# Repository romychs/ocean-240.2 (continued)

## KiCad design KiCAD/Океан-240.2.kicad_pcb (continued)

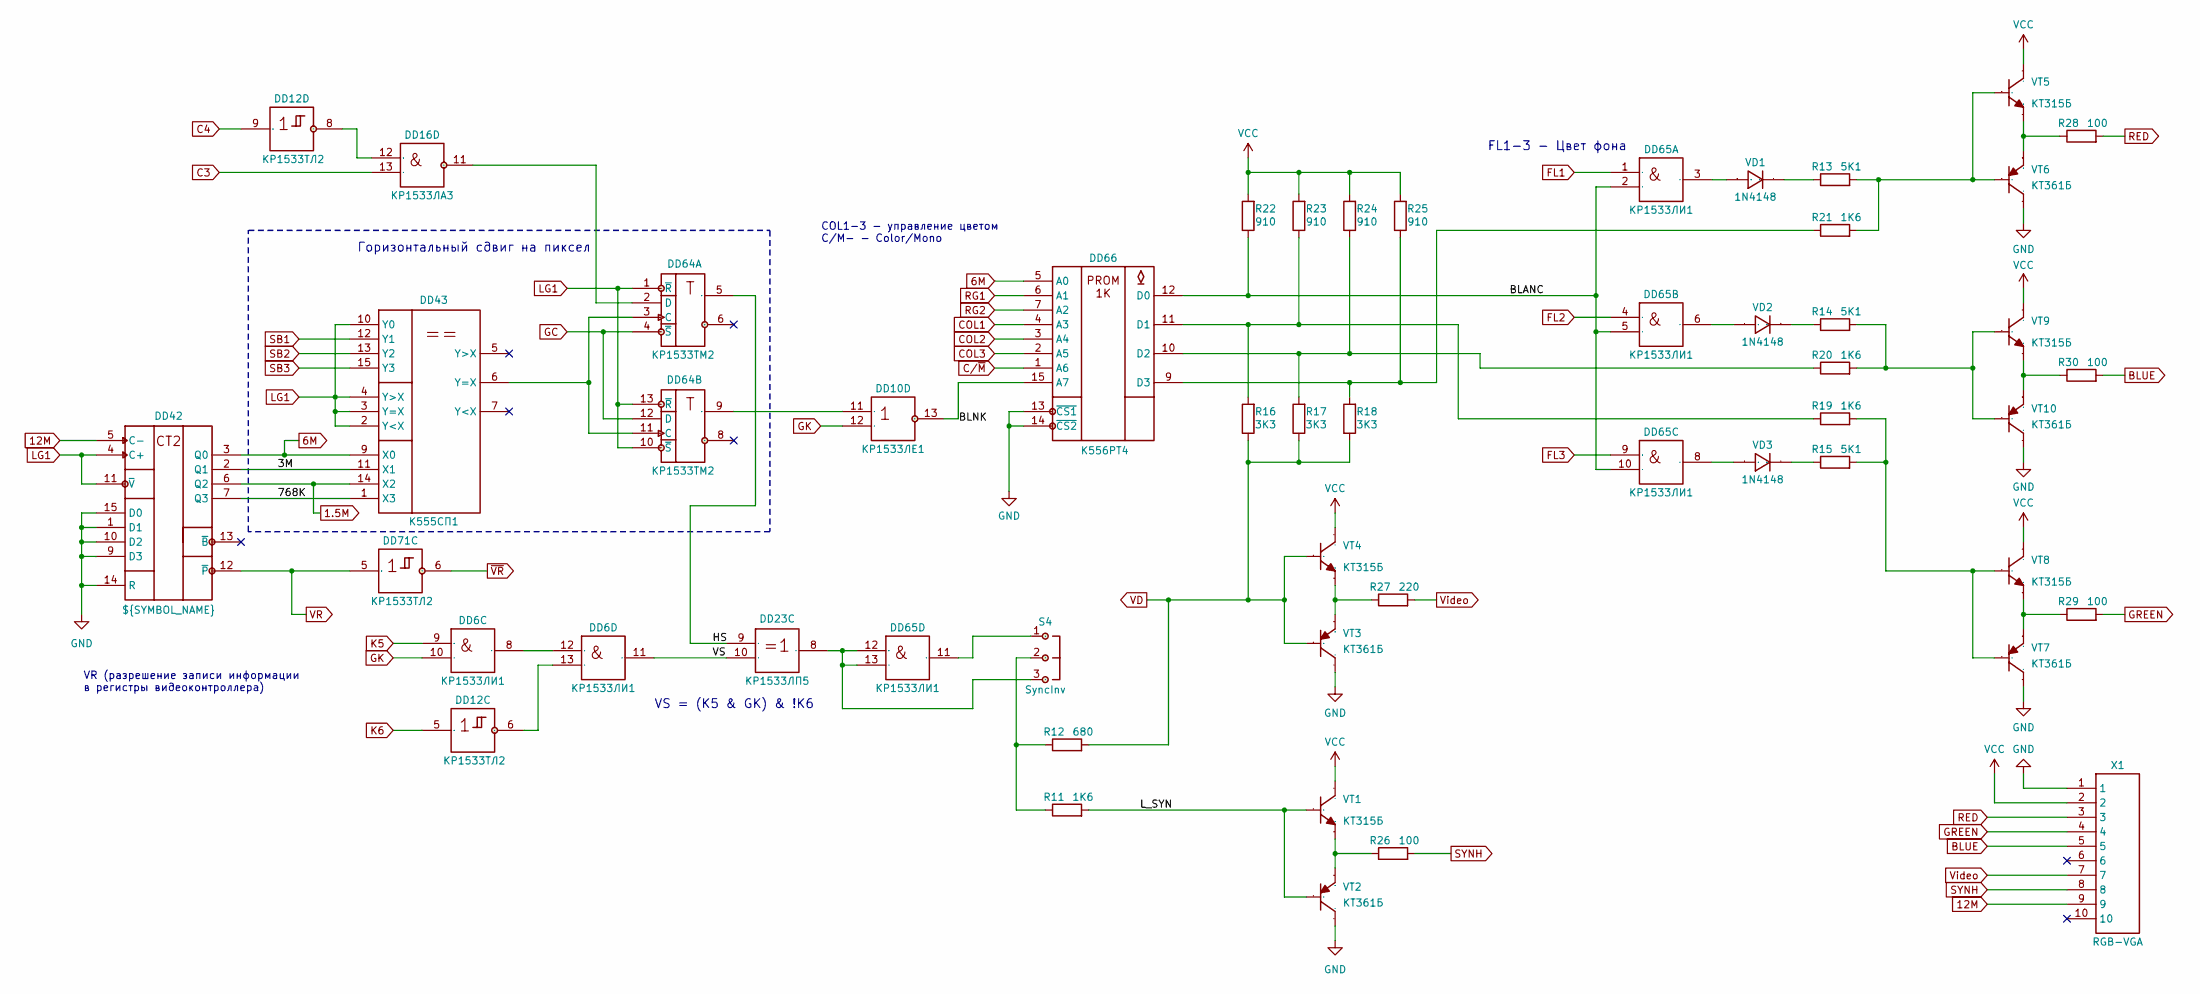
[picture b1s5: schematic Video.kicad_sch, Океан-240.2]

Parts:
DD6, DD65: КР1533ЛИ1; DIP-14_W7.62mm
DD10: КР1533ЛЕ1; DIP-14_W7.62mm
DD12, DD71: КР1533ТЛ2; DIP-14_W7.62mm
DD16: КР1533ЛА3; DIP-14_W7.62mm
DD23: КР1533ЛП5; DIP-14_W7.62mm
DD42: ${SYMBOL_NAME}; DIP-16_W7.62mm
DD43: К555СП1; DIP-16_W7.62mm
DD64: КР1533ТМ2; DIP-14_W7.62mm
DD66: К556РТ4; DIP-16_W7.62mm
R11, R19, R20, R21: 1K6; RES_0.125W_P7.62
R12: 680; RES_0.125W_P7.62
R13, R14, R15: 5K1; RES_0.125W_P7.62
R16, R17, R18: 3K3; RES_0.125W_P7.62
R22, R23, R24, R25: 910; RES_0.125W_P7.62
R26, R28, R29, R30: 100; RES_0.125W_P7.62
R27: 220; RES_0.125W_P7.62
S4: SyncInv; HDR-3P-M-P2.54
VD1, VD2, VD3: 1N4148; DO-35_TH_P7.62
VT1, VT4, VT5, VT8, VT9: КТ315Б; KT315_STD
VT2, VT3, VT6, VT7, VT10: КТ361Б; KT315_STD
X1: RGB-VGA; HDR-10P-M-P2.54

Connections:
1.5M: DD42.6 (Q2), DD43.14 (X2); also elsewhere on the board
6M: DD42.3 (Q0), DD43.9 (X0), DD66.5 (A0); also elsewhere on the board
12M: DD42.5 (C-), X1.9; also elsewhere on the board
/Океан-240.2 - Видео/3M: DD42.2 (Q1), DD43.11 (X1)
/Океан-240.2 - Видео/768K: DD42.7 (Q3), DD43.1 (X3)
/Океан-240.2 - Видео/BLANC: DD65.2, DD65.5 (2), DD65.10 (2), DD66.12 (D0), R22.1
/Океан-240.2 - Видео/BLNK: DD10.13 (3), DD66.15 (A7)
/Океан-240.2 - Видео/HS: DD23.9 (1), DD64.5 (Q)
/Океан-240.2 - Видео/L_SYN: R11.2, VT1.3 (B), VT2.3 (B)
/Океан-240.2 - Видео/VS: DD6.11 (3), DD23.10 (2)
BLUE: R30.2, X1.5
C3: DD16.13 (2); also elsewhere on the board
C4: DD12.9 (1); also elsewhere on the board
COL1: DD66.4 (A3); also elsewhere on the board
COL2: DD66.3 (A4); also elsewhere on the board
COL3: DD66.2 (A5); also elsewhere on the board
C/~M: DD66.1 (A6); also elsewhere on the board
FL1: DD65.1; also elsewhere on the board
FL2: DD65.4 (1); also elsewhere on the board
FL3: DD65.9 (1); also elsewhere on the board
GC: DD64.4 (~S), DD64.12 (D); also elsewhere on the board
GK: DD6.10 (2), DD10.12 (2); also elsewhere on the board
GND: DD42.1 (D1), DD42.8 (GND), DD42.9 (D3), DD42.10 (D2), DD42.14 (R), DD42.15 (D0), DD43.8 (GND), DD64.7 (GND), DD65.7 (GND), DD66.8 (GND), DD66.13 (~CS1), DD66.14 (~CS2), VT2.2 (C), VT3.2 (C), VT6.2 (C), VT7.2 (C), VT10.2 (C), X1.1; also elsewhere on the board
GREEN: R29.2, X1.4
K5: DD6.9 (1); also elsewhere on the board
K6: DD12.5 (1); also elsewhere on the board
LG1: DD42.4 (C+), DD42.11 (~V), DD43.2 (Y<X), DD43.3 (Y=X), DD43.4 (Y>X), DD43.10 (Y0), DD64.1 (~R), DD64.10 (~S), DD64.13 (~R); also elsewhere on the board
unnamed: DD6.8 (3), DD6.12 (1)
unnamed: DD10.11 (1), DD64.9 (Q)
unnamed: DD6.13 (2), DD12.6 (2)
unnamed: DD12.8 (2), DD16.12 (1)
unnamed: DD16.11 (3), DD64.2 (D)
unnamed: DD23.8 (3), DD65.12 (1), DD65.13 (2), S4.3
unnamed: DD43.6 (Y=X), DD64.3 (С), DD64.11 (С)
unnamed: DD65.6 (3), VD2.1 (A)
unnamed: DD65.8 (3), VD3.1 (A)
unnamed: DD65.11 (3), S4.1
unnamed: DD66.11 (D1), R16.2, R19.1, R23.1
unnamed: DD66.10 (D2), R17.2, R20.1, R24.1
unnamed: DD66.9 (D3), R18.2, R21.1, R25.1
unnamed: R11.1, R12.1, S4.2
unnamed: DD65.3, VD1.1 (A)
unnamed: R13.1, VD1.2 (K)
unnamed: R14.1, VD2.2 (K)
unnamed: R15.1, VD3.2 (K)
unnamed: R26.1, VT1.1 (E), VT2.1 (E)
unnamed: R27.1, VT3.1 (E), VT4.1 (E)
unnamed: R13.2, R21.2, VT5.3 (B), VT6.3 (B)
unnamed: R28.1, VT5.1 (E), VT6.1 (E)
unnamed: R15.2, R19.2, VT7.3 (B), VT8.3 (B)
unnamed: R29.1, VT7.1 (E), VT8.1 (E)
unnamed: R14.2, R20.2, VT9.3 (B), VT10.3 (B)
unnamed: R30.1, VT9.1 (E), VT10.1 (E)
RED: R28.2, X1.3
RG1: DD66.6 (A1); also elsewhere on the board
RG2: DD66.7 (A2); also elsewhere on the board
SB1: DD43.12 (Y1); also elsewhere on the board
SB2: DD43.13 (Y2); also elsewhere on the board
SB3: DD43.15 (Y3); also elsewhere on the board
SYNH: R26.2, X1.8
VCC: DD42.16 (VCC), DD43.16 (VCC), DD64.14 (VCC), DD65.14 (VCC), DD66.16 (VCC), R22.2, R23.2, R24.2, R25.2, VT1.2 (C), VT4.2 (C), VT5.2 (C), VT8.2 (C), VT9.2 (C), X1.2; also elsewhere on the board
VD: R12.2, R16.1, R17.1, R18.1, VT3.3 (B), VT4.3 (B)
VR: DD42.12 (~P), DD71.5 (1); also elsewhere on the board
Video: R27.2, X1.7
~VR: DD71.6 (2); also elsewhere on the board

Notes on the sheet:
FL1-3 - Цвет фона
VR (разрешение записи информации в регистры видеоконтроллера)
COL1-3 - управление цветом C/M- - Color/Mono
VS = (K5 & GK) & !K6
Горизонтальный сдвиг на пиксел

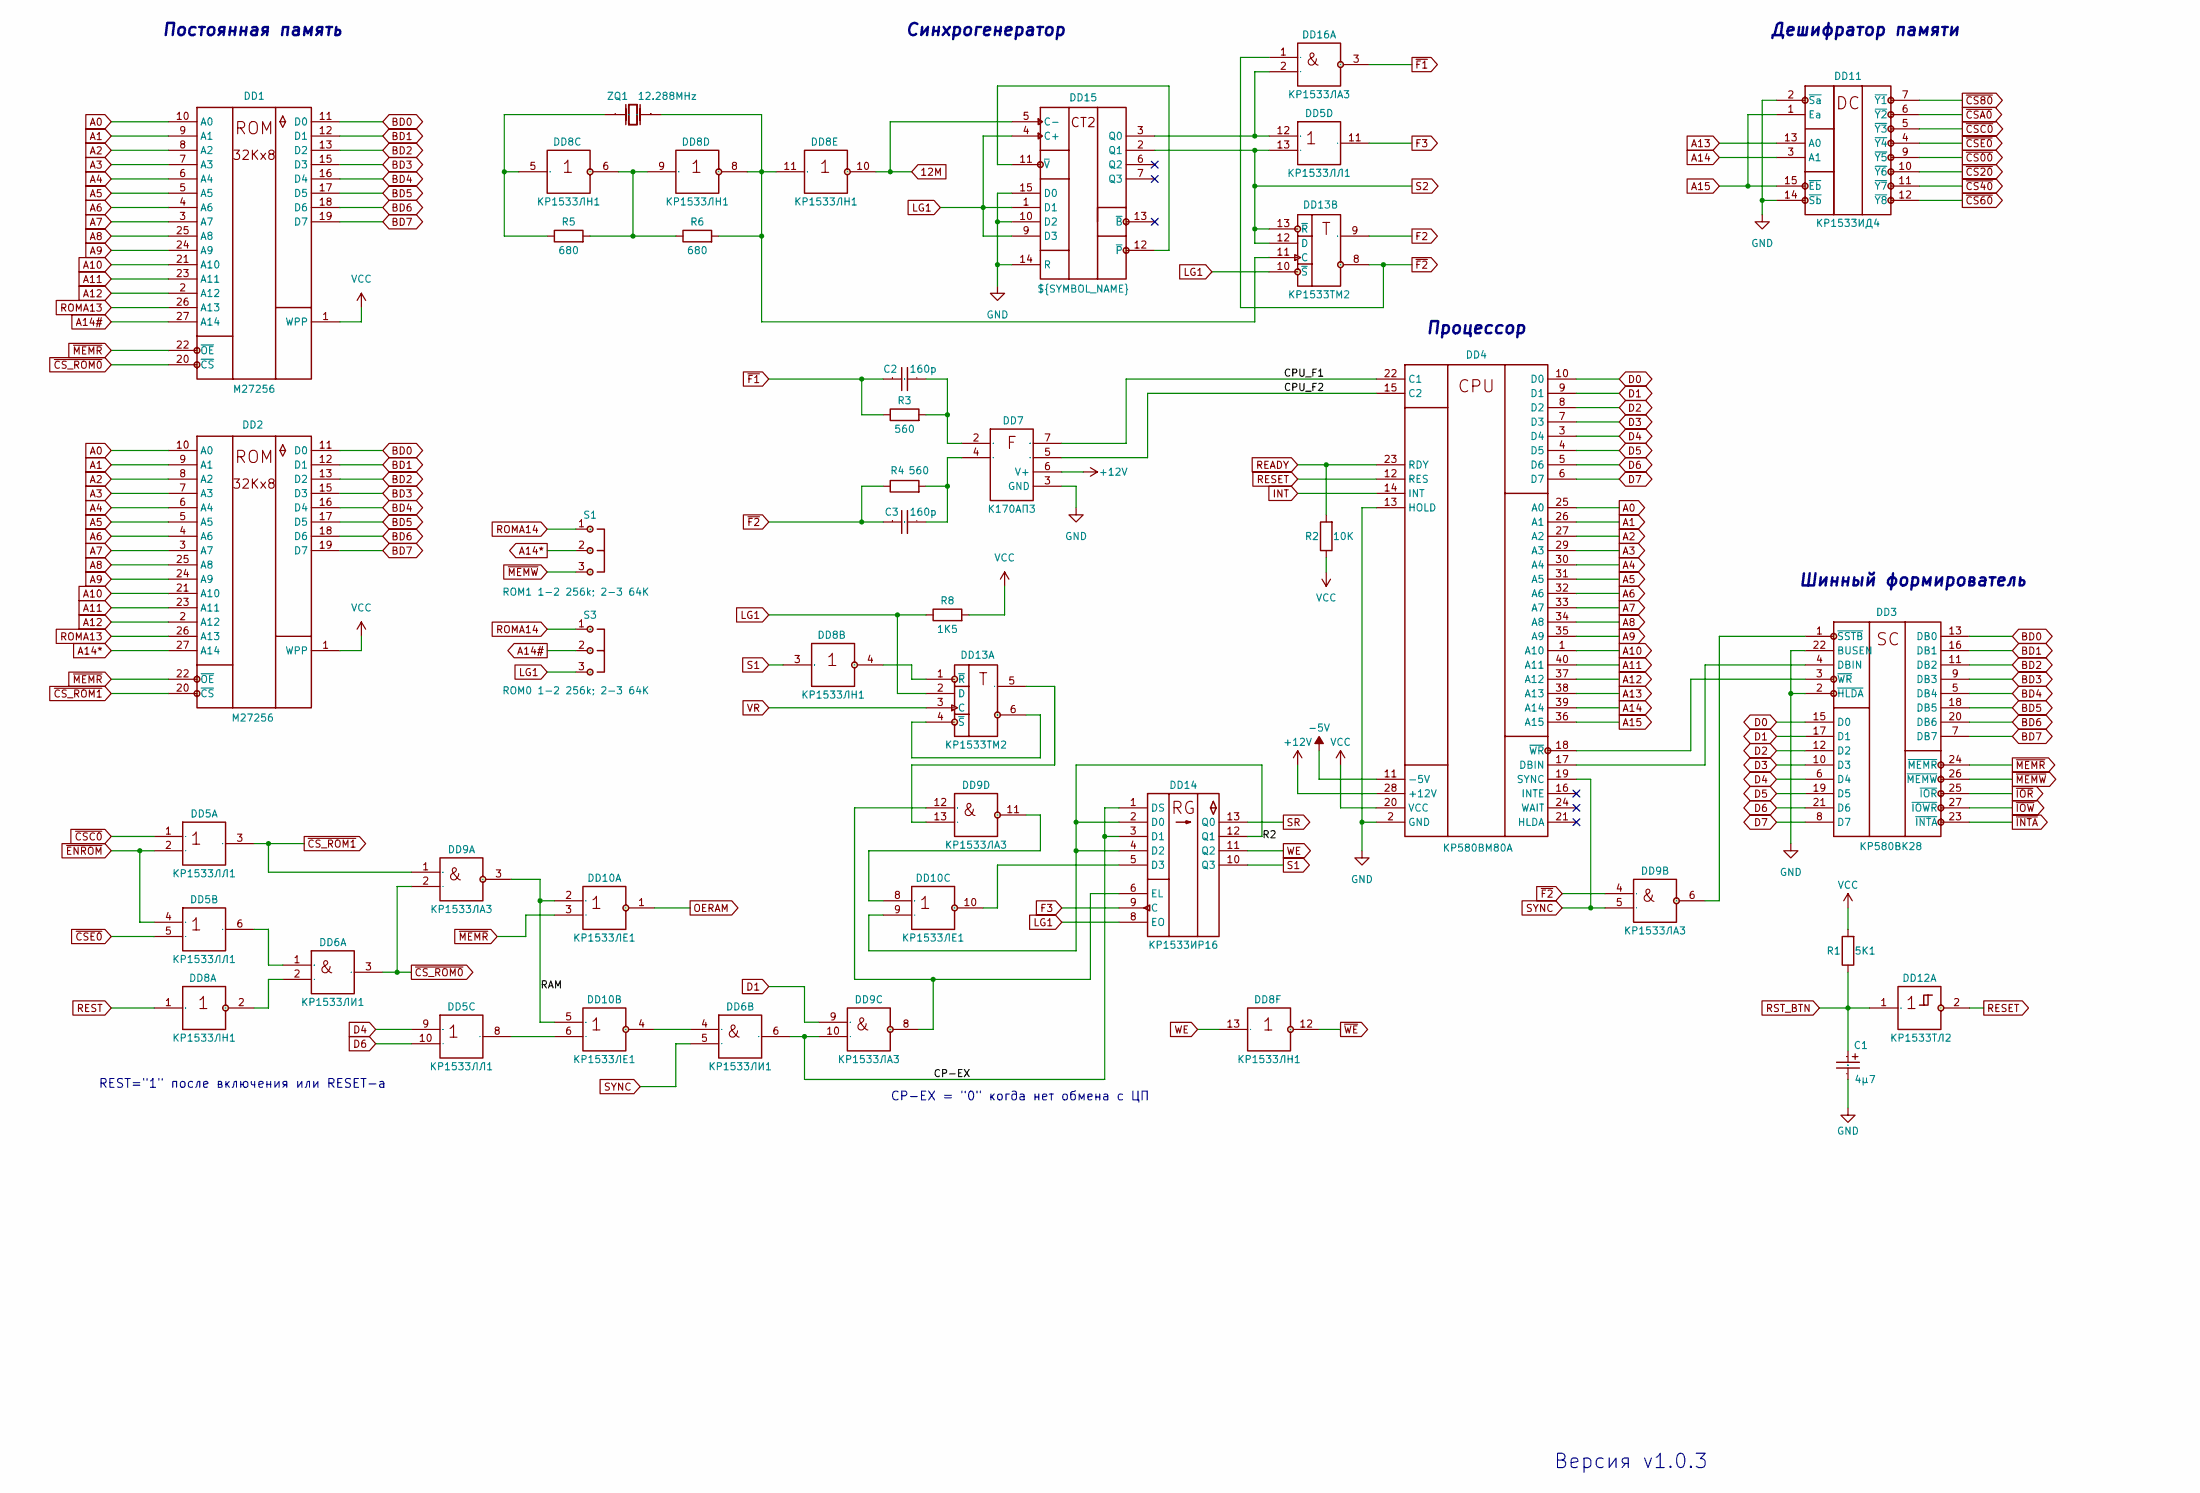
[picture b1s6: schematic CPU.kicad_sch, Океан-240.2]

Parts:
C1: 4μ7; CAP_P-TH-5x11-P2.54
C2, C3: 160p; CAP-TH_L7.62
DD1, DD2: M27256; DIP-28_W15.24mm_Socket
DD3: КР580ВК28; DIP-28_W15.24mm
DD4: КР580ВМ80А; DIP-40_W15.24mm_Socket
DD5: КР1533ЛЛ1; DIP-14_W7.62mm
DD6: КР1533ЛИ1; DIP-14_W7.62mm
DD7: К170АП3; DIP-8_W7.62mm
DD8: КР1533ЛН1; DIP-14_W7.62mm
DD9, DD16: КР1533ЛА3; DIP-14_W7.62mm
DD10: КР1533ЛЕ1; DIP-14_W7.62mm
DD11: КР1533ИД4; DIP-16_W7.62mm
DD12: КР1533ТЛ2; DIP-14_W7.62mm
DD13: КР1533ТМ2; DIP-14_W7.62mm
DD14: КР1533ИР16; DIP-14_W7.62mm
DD15: ${SYMBOL_NAME}; DIP-16_W7.62mm
R1: 5K1; RES_0.125W_P7.62
R2: 10K; RES_0.125W_P7.62
R3, R4: 560; RES_0.125W_P7.62
R5, R6: 680; RES_0.125W_P7.62
R8: 1K5; RES_0.125W_P7.62
S1: ROM1 1-2 256k; 2-3 64K; HDR-3P-M-P2.54
S3: ROM0 1-2 256k; 2-3 64K; HDR-3P-M-P2.54
ZQ1: 12.288MHz; Crystal_HC49-U_Vertical

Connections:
12M: DD8.10 (2), DD15.5 (C-); also elsewhere on the board
+12V: DD4.28 (+12V), DD7.6 (V+); also elsewhere on the board
-5V: DD4.11 (-5V); also elsewhere on the board
/Океан-240.2 - ЦПУ, ПЗУ, синхронизация/CP-EX: DD6.6 (3), DD9.10 (2), DD14.1 (DS), DD14.3 (D1)
/Океан-240.2 - ЦПУ, ПЗУ, синхронизация/CPU_F1: DD4.22 (С1), DD7.7 (O1)
/Океан-240.2 - ЦПУ, ПЗУ, синхронизация/CPU_F2: DD4.15 (С2), DD7.5 (O2)
/Океан-240.2 - ЦПУ, ПЗУ, синхронизация/R2: DD10.9 (2), DD14.2 (D0), DD14.4 (D2), DD14.12 (Q1)
/Океан-240.2 - ЦПУ, ПЗУ, синхронизация/RAM: DD9.3, DD10.2 (1), DD10.5 (1)
A0: DD1.10 (A0), DD2.10 (A0), DD4.25 (A0); also elsewhere on the board
A1: DD1.9 (A1), DD2.9 (A1), DD4.26 (A1); also elsewhere on the board
A2: DD1.8 (A2), DD2.8 (A2), DD4.27 (A2); also elsewhere on the board
A3: DD1.7 (A3), DD2.7 (A3), DD4.29 (A3); also elsewhere on the board
A4: DD1.6 (A4), DD2.6 (A4), DD4.30 (A4); also elsewhere on the board
A5: DD1.5 (A5), DD2.5 (A5), DD4.31 (A5); also elsewhere on the board
A6: DD1.4 (A6), DD2.4 (A6), DD4.32 (A6); also elsewhere on the board
A7: DD1.3 (A7), DD2.3 (A7), DD4.33 (A7); also elsewhere on the board
A8: DD1.25 (A8), DD2.25 (A8), DD4.34 (A8); also elsewhere on the board
A9: DD1.24 (A9), DD2.24 (A9), DD4.35 (A9); also elsewhere on the board
A10: DD1.21 (A10), DD2.21 (A10), DD4.1 (A10); also elsewhere on the board
A11: DD1.23 (A11), DD2.23 (A11), DD4.40 (A11); also elsewhere on the board
A12: DD1.2 (A12), DD2.2 (A12), DD4.37 (A12); also elsewhere on the board
A13: DD4.38 (A13), DD11.13 (A0); also elsewhere on the board
A14: DD4.39 (A14), DD11.3 (A1); also elsewhere on the board
A14#: DD1.27 (A14), S3.2
A14*: DD2.27 (A14), S1.2
A15: DD4.36 (A15), DD11.1 (Ea), DD11.15 (~Eb); also elsewhere on the board
BD0: DD1.11 (D0), DD2.11 (D0), DD3.13 (DB0); also elsewhere on the board
BD1: DD1.12 (D1), DD2.12 (D1), DD3.16 (DB1); also elsewhere on the board
BD2: DD1.13 (D2), DD2.13 (D2), DD3.11 (DB2); also elsewhere on the board
BD3: DD1.15 (D3), DD2.15 (D3), DD3.9 (DB3); also elsewhere on the board
BD4: DD1.16 (D4), DD2.16 (D4), DD3.5 (DB4); also elsewhere on the board
BD5: DD1.17 (D5), DD2.17 (D5), DD3.18 (DB5); also elsewhere on the board
BD6: DD1.18 (D6), DD2.18 (D6), DD3.20 (DB6); also elsewhere on the board
BD7: DD1.19 (D7), DD2.19 (D7), DD3.7 (DB7); also elsewhere on the board
D0: DD3.15 (D0), DD4.10 (D0); also elsewhere on the board
D1: DD3.17 (D1), DD4.9 (D1), DD9.9 (1); also elsewhere on the board
D2: DD3.12 (D2), DD4.8 (D2); also elsewhere on the board
D3: DD3.10 (D3), DD4.7 (D3); also elsewhere on the board
D4: DD3.6 (D4), DD4.3 (D4), DD5.9 (1); also elsewhere on the board
D5: DD3.19 (D5), DD4.4 (D5); also elsewhere on the board
D6: DD3.21 (D6), DD4.5 (D6), DD5.10 (2); also elsewhere on the board
D7: DD3.8 (D7), DD4.6 (D7); also elsewhere on the board
F2: DD13.9 (Q); also elsewhere on the board
F3: DD5.11 (3), DD14.9 (C); also elsewhere on the board
GND: C1.2, DD1.14 (GND), DD2.14 (GND), DD3.2 (~HLDA), DD3.14 (GND), DD3.22 (BUSEN), DD4.2 (GND), DD4.13 (HOLD), DD5.7 (GND), DD6.7 (GND), DD7.3 (GND), DD8.7 (GND), DD9.7 (GND), DD10.7 (GND), DD11.2 (~Sa), DD11.8 (GND), DD11.14 (~Sb), DD12.7 (GND), DD13.7 (GND), DD14.7 (GND), DD15.8 (GND), DD15.10 (D2), DD15.14 (R), DD15.15 (D0), DD16.7 (GND); also elsewhere on the board
INT: DD4.14 (INT); also elsewhere on the board
LG1: DD13.2 (D), DD13.10 (~S), DD14.8 (EO), DD15.1 (D1), DD15.4 (C+), DD15.9 (D3), R8.1, S3.3; also elsewhere on the board
unnamed: DD3.4 (DBIN), DD4.17 (DBIN)
unnamed: DD3.1 (~SSTB), DD9.6 (3)
unnamed: DD3.3 (~WR), DD4.18 (~WR)
unnamed: DD5.6 (3), DD6.1
unnamed: DD6.2, DD8.2
unnamed: C2.2, DD7.2 (I1), R3.2
unnamed: C3.2, DD7.4 (I2), R4.2
unnamed: DD8.5 (1), R5.1, ZQ1.2 (OSC2)
unnamed: DD8.6 (2), DD8.9 (1), R5.2, R6.1
unnamed: DD5.8 (3), DD10.6 (2)
unnamed: DD6.4 (1), DD10.4 (3)
unnamed: DD9.11 (3), DD10.8 (1)
unnamed: DD10.10 (3), DD14.5 (D3)
unnamed: DD9.13 (2), DD13.5 (Q)
unnamed: DD13.4 (~S), DD13.6 (~Q)
unnamed: DD8.4 (2), DD13.1 (~R)
unnamed: DD8.8 (2), DD8.11 (1), DD13.11 (С), R6.2, ZQ1.1 (OSC1)
unnamed: DD9.8 (3), DD9.12 (1), DD14.6 (EL)
unnamed: DD5.12 (1), DD15.3 (Q0), DD16.2
unnamed: DD15.11 (~V), DD15.12 (~P)
OERAM: DD10.1 (3); also elsewhere on the board
READY: DD4.23 (RDY), R2.2; also elsewhere on the board
RESET: DD4.12 (RES), DD12.2; also elsewhere on the board
REST: DD8.1; also elsewhere on the board
ROMA13: DD1.26 (A13), DD2.26 (A13); also elsewhere on the board
ROMA14: S1.1, S3.1; also elsewhere on the board
RST_BTN: C1.1, DD12.1, R1.1; also elsewhere on the board
S1: DD8.3 (1), DD14.10 (Q3); also elsewhere on the board
S2: DD5.13 (2), DD13.12 (D), DD13.13 (~R), DD15.2 (Q1); also elsewhere on the board
SR: DD14.13 (Q0); also elsewhere on the board
SYNC: DD4.19 (SYNC), DD6.5 (2), DD9.5 (2)
VCC: DD1.1 (WPP), DD1.28 (VCC), DD2.1 (WPP), DD2.28 (VCC), DD3.28 (VCC), DD4.20 (VCC), DD5.14 (VCC), DD6.14 (VCC), DD8.14 (VCC), DD9.14 (VCC), DD10.14 (VCC), DD11.16 (VCC), DD12.14 (VCC), DD13.14 (VCC), DD14.14 (VCC), DD15.16 (VCC), DD16.14 (VCC), R1.2, R2.1, R8.2; also elsewhere on the board
VR: DD13.3 (С); also elsewhere on the board
WE: DD8.13 (1), DD14.11 (Q2)
~CS00: DD11.9 (~Y5); also elsewhere on the board
~CS20: DD11.10 (~Y6); also elsewhere on the board
~CS40: DD11.11 (~Y7); also elsewhere on the board
~CS60: DD11.12 (~Y8); also elsewhere on the board
~CS80: DD11.7 (~Y1); also elsewhere on the board
~CSA0: DD11.6 (~Y2); also elsewhere on the board
~CSC0: DD5.1, DD11.5 (~Y3); also elsewhere on the board
~CSE0: DD5.5 (2), DD11.4 (~Y4); also elsewhere on the board
~CS_ROM0: DD1.20 (~CS), DD6.3, DD9.2
~CS_ROM1: DD2.20 (~CS), DD5.3, DD9.1
~ENROM: DD5.2, DD5.4 (1); also elsewhere on the board
~F1: C2.1, DD16.3, R3.1
~F2: C3.1, DD9.4 (1), DD13.8 (~Q), DD16.1, R4.1
~INTA: DD3.23 (~INTA); also elsewhere on the board
~IOR: DD3.25 (~IOR); also elsewhere on the board
~IOW: DD3.27 (~IOWR); also elsewhere on the board
~MEMR: DD1.22 (~OE), DD2.22 (~OE), DD3.24 (~MEMR), DD10.3 (2)
~MEMW: DD3.26 (~MEMW), S1.3
~WE: DD8.12 (3); also elsewhere on the board

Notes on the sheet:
REST="1" после включения или RESET-а
Версия ${REVISION}
Постоянная память
CP-EX = "0" когда нет обмена с ЦП
Дешифратор памяти
Синхрогенератор
Процессор
Шинный формирователь

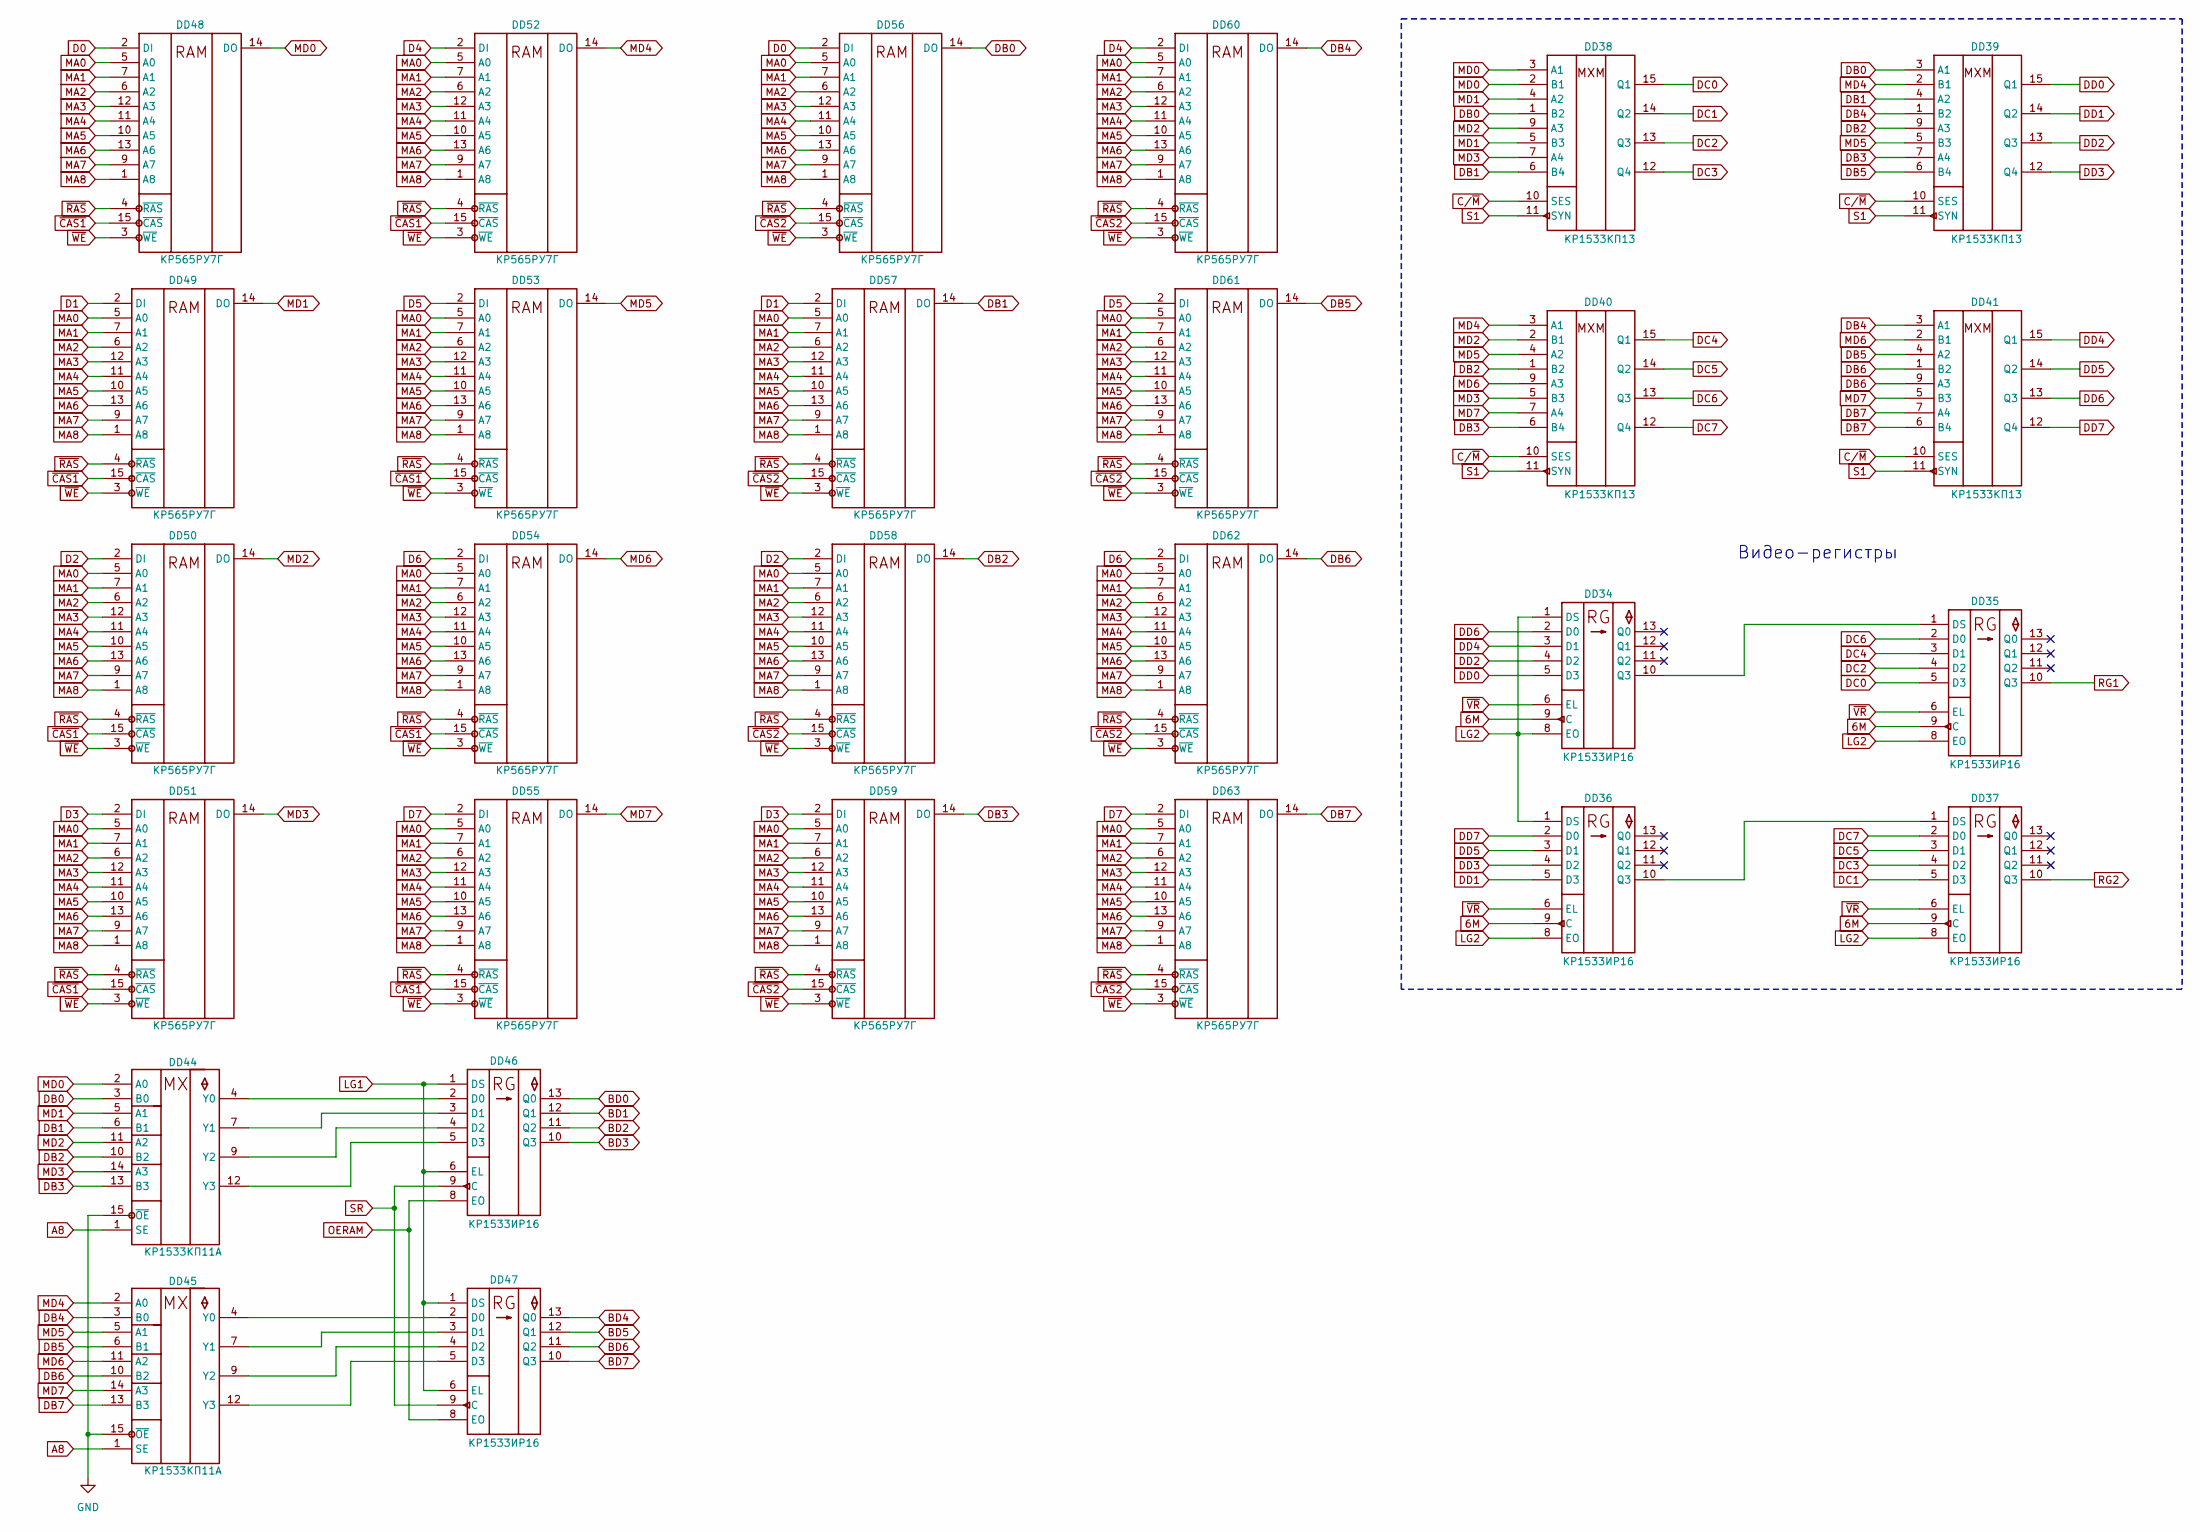
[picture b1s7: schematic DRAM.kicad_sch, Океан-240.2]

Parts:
DD34, DD35, DD36, DD37, DD46, DD47: КР1533ИР16; DIP-14_W7.62mm
DD38, DD39, DD40, DD41: КР1533КП13; DIP-16_W7.62mm
DD44, DD45: КР1533КП11A; DIP-16_W7.62mm
DD48, DD49, DD50, DD51, DD52, DD53, DD54, DD55, DD56, DD57, DD58, DD59, DD60, DD61, DD62, DD63: КР565РУ7Г; DIP-16_W7.62mm_Socket

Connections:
6M: DD34.9 (C), DD35.9 (C), DD36.9 (C), DD37.9 (C); also elsewhere on the board
A8: DD44.1 (SE), DD45.1 (SE); also elsewhere on the board
BD0: DD46.13 (Q0); also elsewhere on the board
BD1: DD46.12 (Q1); also elsewhere on the board
BD2: DD46.11 (Q2); also elsewhere on the board
BD3: DD46.10 (Q3); also elsewhere on the board
BD4: DD47.13 (Q0); also elsewhere on the board
BD5: DD47.12 (Q1); also elsewhere on the board
BD6: DD47.11 (Q2); also elsewhere on the board
BD7: DD47.10 (Q3); also elsewhere on the board
C/~M: DD38.10 (SES), DD39.10 (SES), DD40.10 (SES), DD41.10 (SES); also elsewhere on the board
D0: DD48.2 (DI), DD56.2 (DI); also elsewhere on the board
D1: DD49.2 (DI), DD57.2 (DI); also elsewhere on the board
D2: DD50.2 (DI), DD58.2 (DI); also elsewhere on the board
D3: DD51.2 (DI), DD59.2 (DI); also elsewhere on the board
D4: DD52.2 (DI), DD60.2 (DI); also elsewhere on the board
D5: DD53.2 (DI), DD61.2 (DI); also elsewhere on the board
D6: DD54.2 (DI), DD62.2 (DI); also elsewhere on the board
D7: DD55.2 (DI), DD63.2 (DI); also elsewhere on the board
DB0: DD38.1 (B2), DD39.3 (A1), DD44.3 (B0), DD56.14 (DO)
DB1: DD38.6 (B4), DD39.4 (A2), DD44.6 (B1), DD57.14 (DO)
DB2: DD39.9 (A3), DD40.1 (B2), DD44.10 (B2), DD58.14 (DO)
DB3: DD39.7 (A4), DD40.6 (B4), DD44.13 (B3), DD59.14 (DO)
DB4: DD39.1 (B2), DD41.3 (A1), DD45.3 (B0), DD60.14 (DO)
DB5: DD39.6 (B4), DD41.4 (A2), DD45.6 (B1), DD61.14 (DO)
DB6: DD41.1 (B2), DD41.9 (A3), DD45.10 (B2), DD62.14 (DO)
DB7: DD41.6 (B4), DD41.7 (A4), DD45.13 (B3), DD63.14 (DO)
DC0: DD35.5 (D3), DD38.15 (Q1)
DC1: DD37.5 (D3), DD38.14 (Q2)
DC2: DD35.4 (D2), DD38.13 (Q3)
DC3: DD37.4 (D2), DD38.12 (Q4)
DC4: DD35.3 (D1), DD40.15 (Q1)
DC5: DD37.3 (D1), DD40.14 (Q2)
DC6: DD35.2 (D0), DD40.13 (Q3)
DC7: DD37.2 (D0), DD40.12 (Q4)
DD0: DD34.5 (D3), DD39.15 (Q1)
DD1: DD36.5 (D3), DD39.14 (Q2)
DD2: DD34.4 (D2), DD39.13 (Q3)
DD3: DD36.4 (D2), DD39.12 (Q4)
DD4: DD34.3 (D1), DD41.15 (Q1)
DD5: DD36.3 (D1), DD41.14 (Q2)
DD6: DD34.2 (D0), DD41.13 (Q3)
DD7: DD36.2 (D0), DD41.12 (Q4)
GND: DD34.7 (GND), DD35.7 (GND), DD36.7 (GND), DD37.7 (GND), DD38.8 (GND), DD39.8 (GND), DD40.8 (GND), DD41.8 (GND), DD44.8 (GND), DD44.15 (~OE), DD45.8 (GND), DD45.15 (~OE), DD46.7 (GND), DD47.7 (GND), DD48.16 (GND), DD49.16 (GND), DD50.16 (GND), DD51.16 (GND), DD52.16 (GND), DD53.16 (GND), DD54.16 (GND), DD55.16 (GND), DD56.16 (GND), DD57.16 (GND), DD58.16 (GND), DD59.16 (GND), DD60.16 (GND), DD61.16 (GND), DD62.16 (GND), DD63.16 (GND); also elsewhere on the board
LG1: DD46.1 (DS), DD46.6 (EL), DD47.1 (DS), DD47.6 (EL); also elsewhere on the board
LG2: DD34.1 (DS), DD34.8 (EO), DD35.8 (EO), DD36.1 (DS), DD36.8 (EO), DD37.8 (EO); also elsewhere on the board
MA0: DD48.5 (A0), DD49.5 (A0), DD50.5 (A0), DD51.5 (A0), DD52.5 (A0), DD53.5 (A0), DD54.5 (A0), DD55.5 (A0), DD56.5 (A0), DD57.5 (A0), DD58.5 (A0), DD59.5 (A0), DD60.5 (A0), DD61.5 (A0), DD62.5 (A0), DD63.5 (A0); also elsewhere on the board
MA1: DD48.7 (A1), DD49.7 (A1), DD50.7 (A1), DD51.7 (A1), DD52.7 (A1), DD53.7 (A1), DD54.7 (A1), DD55.7 (A1), DD56.7 (A1), DD57.7 (A1), DD58.7 (A1), DD59.7 (A1), DD60.7 (A1), DD61.7 (A1), DD62.7 (A1), DD63.7 (A1); also elsewhere on the board
MA2: DD48.6 (A2), DD49.6 (A2), DD50.6 (A2), DD51.6 (A2), DD52.6 (A2), DD53.6 (A2), DD54.6 (A2), DD55.6 (A2), DD56.6 (A2), DD57.6 (A2), DD58.6 (A2), DD59.6 (A2), DD60.6 (A2), DD61.6 (A2), DD62.6 (A2), DD63.6 (A2); also elsewhere on the board
MA3: DD48.12 (A3), DD49.12 (A3), DD50.12 (A3), DD51.12 (A3), DD52.12 (A3), DD53.12 (A3), DD54.12 (A3), DD55.12 (A3), DD56.12 (A3), DD57.12 (A3), DD58.12 (A3), DD59.12 (A3), DD60.12 (A3), DD61.12 (A3), DD62.12 (A3), DD63.12 (A3); also elsewhere on the board
MA4: DD48.11 (A4), DD49.11 (A4), DD50.11 (A4), DD51.11 (A4), DD52.11 (A4), DD53.11 (A4), DD54.11 (A4), DD55.11 (A4), DD56.11 (A4), DD57.11 (A4), DD58.11 (A4), DD59.11 (A4), DD60.11 (A4), DD61.11 (A4), DD62.11 (A4), DD63.11 (A4); also elsewhere on the board
MA5: DD48.10 (A5), DD49.10 (A5), DD50.10 (A5), DD51.10 (A5), DD52.10 (A5), DD53.10 (A5), DD54.10 (A5), DD55.10 (A5), DD56.10 (A5), DD57.10 (A5), DD58.10 (A5), DD59.10 (A5), DD60.10 (A5), DD61.10 (A5), DD62.10 (A5), DD63.10 (A5); also elsewhere on the board
MA6: DD48.13 (A6), DD49.13 (A6), DD50.13 (A6), DD51.13 (A6), DD52.13 (A6), DD53.13 (A6), DD54.13 (A6), DD55.13 (A6), DD56.13 (A6), DD57.13 (A6), DD58.13 (A6), DD59.13 (A6), DD60.13 (A6), DD61.13 (A6), DD62.13 (A6), DD63.13 (A6); also elsewhere on the board
MA7: DD48.9 (A7), DD49.9 (A7), DD50.9 (A7), DD51.9 (A7), DD52.9 (A7), DD53.9 (A7), DD54.9 (A7), DD55.9 (A7), DD56.9 (A7), DD57.9 (A7), DD58.9 (A7), DD59.9 (A7), DD60.9 (A7), DD61.9 (A7), DD62.9 (A7), DD63.9 (A7); also elsewhere on the board
MA8: DD48.1 (A8), DD49.1 (A8), DD50.1 (A8), DD51.1 (A8), DD52.1 (A8), DD53.1 (A8), DD54.1 (A8), DD55.1 (A8), DD56.1 (A8), DD57.1 (A8), DD58.1 (A8), DD59.1 (A8), DD60.1 (A8), DD61.1 (A8), DD62.1 (A8), DD63.1 (A8); also elsewhere on the board
MD0: DD38.2 (B1), DD38.3 (A1), DD44.2 (A0), DD48.14 (DO)
MD1: DD38.4 (A2), DD38.5 (B3), DD44.5 (A1), DD49.14 (DO)
MD2: DD38.9 (A3), DD40.2 (B1), DD44.11 (A2), DD50.14 (DO)
MD3: DD38.7 (A4), DD40.5 (B3), DD44.14 (A3), DD51.14 (DO)
MD4: DD39.2 (B1), DD40.3 (A1), DD45.2 (A0), DD52.14 (DO)
MD5: DD39.5 (B3), DD40.4 (A2), DD45.5 (A1), DD53.14 (DO)
MD6: DD40.9 (A3), DD41.2 (B1), DD45.11 (A2), DD54.14 (DO)
MD7: DD40.7 (A4), DD41.5 (B3), DD45.14 (A3), DD55.14 (DO)
unnamed: DD34.10 (Q3), DD35.1 (DS)
unnamed: DD36.10 (Q3), DD37.1 (DS)
unnamed: DD44.4 (Y0), DD46.2 (D0)
unnamed: DD44.7 (Y1), DD46.3 (D1)
unnamed: DD44.9 (Y2), DD46.4 (D2)
unnamed: DD44.12 (Y3), DD46.5 (D3)
unnamed: DD45.4 (Y0), DD47.2 (D0)
unnamed: DD45.7 (Y1), DD47.3 (D1)
unnamed: DD45.9 (Y2), DD47.4 (D2)
unnamed: DD45.12 (Y3), DD47.5 (D3)
OERAM: DD46.8 (EO), DD47.8 (EO); also elsewhere on the board
RG1: DD35.10 (Q3); also elsewhere on the board
RG2: DD37.10 (Q3); also elsewhere on the board
S1: DD38.11 (SYN), DD39.11 (SYN), DD40.11 (SYN), DD41.11 (SYN); also elsewhere on the board
SR: DD46.9 (C), DD47.9 (C); also elsewhere on the board
VCC: DD34.14 (VCC), DD35.14 (VCC), DD36.14 (VCC), DD37.14 (VCC), DD38.16 (VCC), DD39.16 (VCC), DD40.16 (VCC), DD41.16 (VCC), DD44.16 (VCC), DD45.16 (VCC), DD46.14 (VCC), DD47.14 (VCC), DD48.8 (VCC), DD49.8 (VCC), DD50.8 (VCC), DD51.8 (VCC), DD52.8 (VCC), DD53.8 (VCC), DD54.8 (VCC), DD55.8 (VCC), DD56.8 (VCC), DD57.8 (VCC), DD58.8 (VCC), DD59.8 (VCC), DD60.8 (VCC), DD61.8 (VCC), DD62.8 (VCC), DD63.8 (VCC); also elsewhere on the board
~CAS1: DD48.15 (~CAS), DD49.15 (~CAS), DD50.15 (~CAS), DD51.15 (~CAS), DD52.15 (~CAS), DD53.15 (~CAS), DD54.15 (~CAS), DD55.15 (~CAS); also elsewhere on the board
~CAS2: DD56.15 (~CAS), DD57.15 (~CAS), DD58.15 (~CAS), DD59.15 (~CAS), DD60.15 (~CAS), DD61.15 (~CAS), DD62.15 (~CAS), DD63.15 (~CAS); also elsewhere on the board
~RAS: DD48.4 (~RAS), DD49.4 (~RAS), DD50.4 (~RAS), DD51.4 (~RAS), DD52.4 (~RAS), DD53.4 (~RAS), DD54.4 (~RAS), DD55.4 (~RAS), DD56.4 (~RAS), DD57.4 (~RAS), DD58.4 (~RAS), DD59.4 (~RAS), DD60.4 (~RAS), DD61.4 (~RAS), DD62.4 (~RAS), DD63.4 (~RAS); also elsewhere on the board
~VR: DD34.6 (EL), DD35.6 (EL), DD36.6 (EL), DD37.6 (EL); also elsewhere on the board
~WE: DD48.3 (~WE), DD49.3 (~WE), DD50.3 (~WE), DD51.3 (~WE), DD52.3 (~WE), DD53.3 (~WE), DD54.3 (~WE), DD55.3 (~WE), DD56.3 (~WE), DD57.3 (~WE), DD58.3 (~WE), DD59.3 (~WE), DD60.3 (~WE), DD61.3 (~WE), DD62.3 (~WE), DD63.3 (~WE); also elsewhere on the board

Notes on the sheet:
Видео-регистры

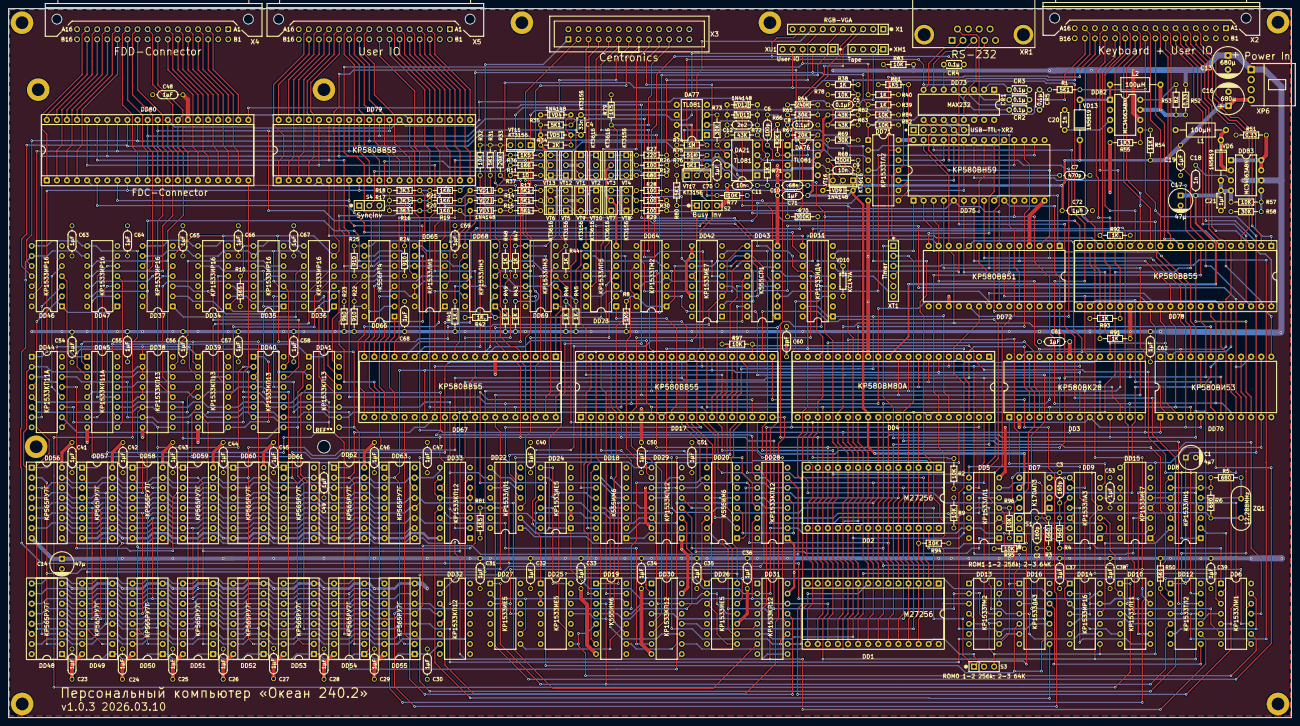
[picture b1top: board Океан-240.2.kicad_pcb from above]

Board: 2 copper layers, 323.3 x 178.7 mm, 285 parts (0 on the bottom side), 430 nets.

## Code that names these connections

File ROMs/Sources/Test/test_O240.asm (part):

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; КР580ВВ55 Порты A и С, B5-7 - Клавиатура
DD78RA		EQU		0x40							; VV55 [Keyboard]
DD78RB		EQU		0x41							; [JST3..1,ACK,TAPE5,TAPE4,GK,GC]
DD78RC		EQU		0x42							; VV55 [PC7..0]
DD78RR		EQU		0x43							; VV55 KBD CTL

; КР580ВВ55 Для внешних устройств пользователя
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	OUT		(DD67RB), A
	LD		A, 0x07									; 0000 0111 -> H Shift HS=00000, SB=111
	OUT		(DD17RC), A
	LD		A, 0x04									; 0000 0100 -> TAPE3 = 1
	OUT		(DD67RC), A

	; Программирование порта ВВ51
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	ADD		A, A
	ADD		A, A
	OR		0x80
	OUT		(DD67RB), A							; VSU=1
	INC		E
	LD		A, E
	CP		0x07
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MSG_DLY1
	DEC		A
	JP		NZ, MSG_DLY1
	LD		A, 0x0C								; 0000 1100  [STB,BELL]=00 [TAPE3..2]=11
	OUT		(DD67RC), A
	LD		A, D
	OR		A
	LD		A, 0x3C								; 0011 1100  [STB,BELL]=11 [TAPE3..2]=11
	JP		Z, MSG_DLY2
	LD		A, 120
MSG_DLY2
	DEC		A
	JP		NZ, MSG_DLY2
	LD		A, 0x04								; 0000 0100 [TAPE3]=1
	OUT		(DD67RC), A
	DEC		B
	JP		NZ, MSG_RPT1
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	RRA
	RRA
	AND		0x01
	; PC0 <- 0/1 - осн/доп ОЗУ
	OUT		(DD80RC),A
	ADD		A, 0x30
	LD		B, A
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
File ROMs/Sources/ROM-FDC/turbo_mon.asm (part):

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
	; config LPT
    LD	A, 0x4
    OUT	(DD67PC), A		    						; bell=1, strobe=0
    LD	(TM_VARS.m_strobe_state), A	   				; store strobe
    LD	HL,1024			   							; 683us
    LD	(TM_VARS.m_beep_period), HL
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    IN	A, (KBD_DD78PA)
    OR	A
    JP	NZ, mc_has_key
    LD	A, KBD_ACK									; ACK=1
    OUT	(KBD_DD78PC), A
    XOR	A
    OUT	(KBD_DD78PC), A								; ACK=0
    XOR	A
    RET

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    AND	00110000b			 						; SHIFT+CTRL
    OR	C
    LD	C, A			       						; C=SHIFT+CTRL+IE10
    LD	A,KBD_ACK			 						; ACK=1
    OUT	(KBD_DD78PC), A
    XOR	A											; ACK=0
    OUT	(KBD_DD78PC), A
    LD	A,B			       							; A = key
    LD	B, 0xff
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    RET	Z											; ret if enough
    DEC	DE
    LD	A,B
    XOR	BELL_PIN
    LD	B, A
    OUT	(DD67PC), A									; Invert bell pin
m_bell_wait_tmr1:
    IN	A, (PIC_DD75RS)
    AND	TIMER_IRQ									; 0x10
    JP	NZ,m_bell_wait_tmr1
    LD	A,B
    XOR	BELL_PIN									; Flip pin again
    LD	B, A
    OUT	(DD67PC), A
m_bell_wait_tmr2:
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tm_beeep:
    LD	BC, 0x6060
tm_bell_next_p:
    LD	A,BELL_PIN
    OUT	(DD67PC), A		    						; BELL=1
    LD	A, C
tm_bell_w1:
    DEC	A
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
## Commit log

2025-08-18 new render
2025-08-18 BOM added
2025-08-19 Source code for TEST ROM
2025-09-08 Sources for ROMs. Light PCB and Schematics fixes
2025-09-08 fix readme
2025-10-03 Light schematics fixes
2025-12-13 Port to KiCAD v9.0
2025-12-13 Preview for KiCAD variant
2026-03-10 Fix DD5 and DD22
2026-03-10 fix ref to gerber
